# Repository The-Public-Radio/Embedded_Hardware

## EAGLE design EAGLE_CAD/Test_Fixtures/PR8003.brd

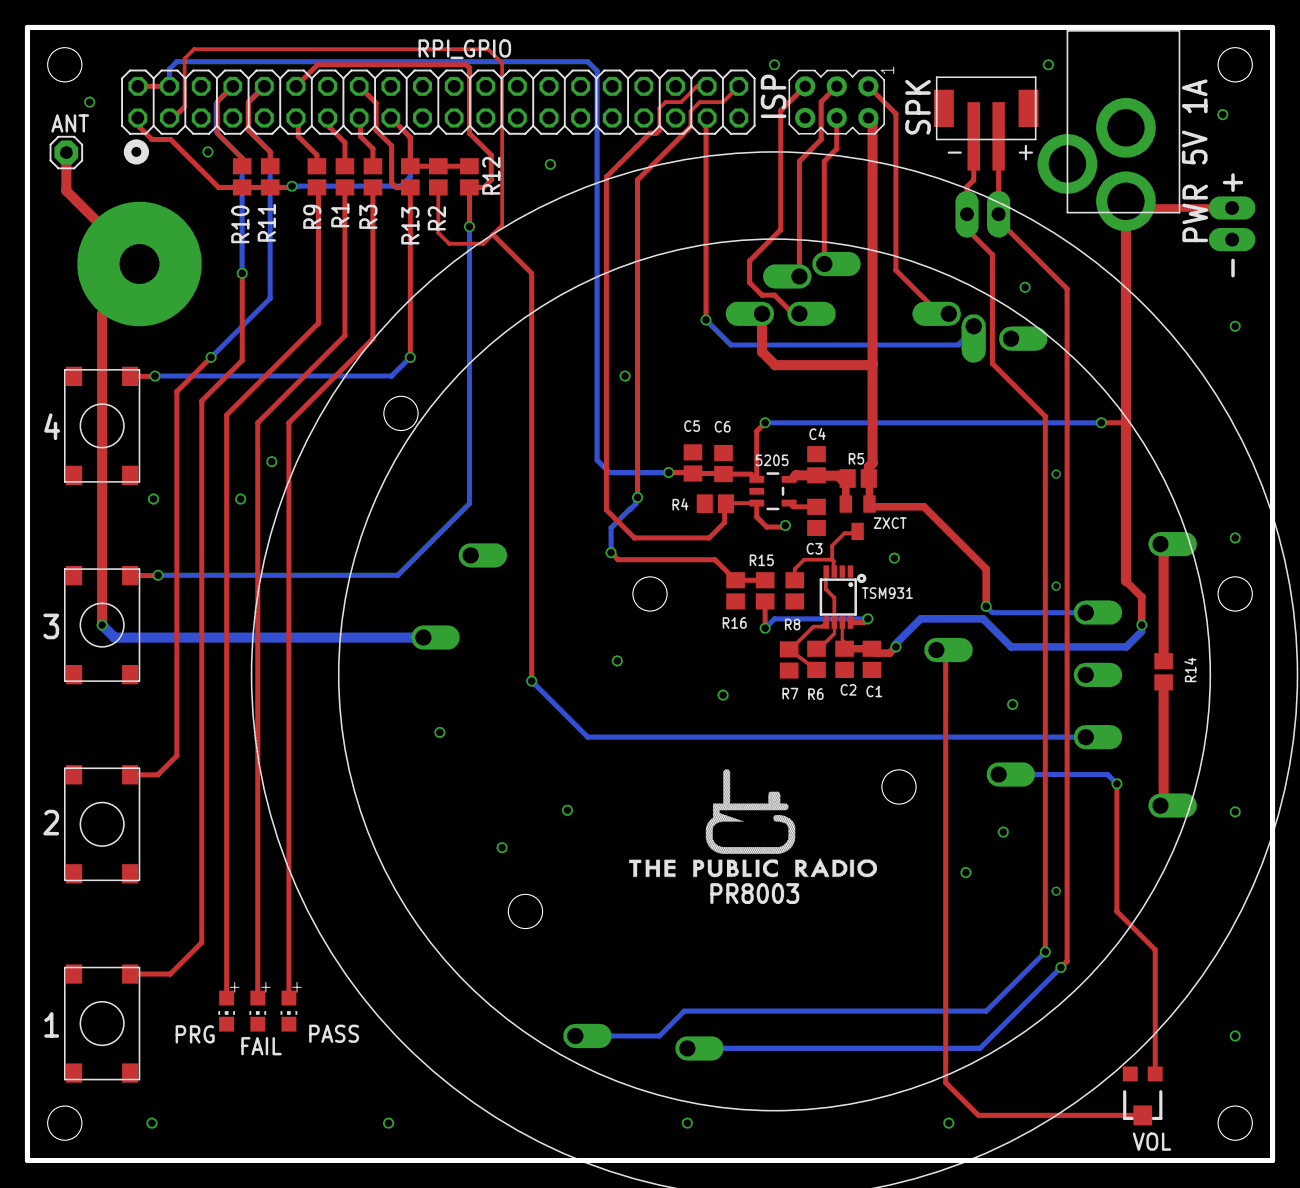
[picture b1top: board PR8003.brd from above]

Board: 2 copper layers, 100.0 x 91.0 mm, 43 parts (0 on the bottom side), 35 nets.

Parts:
5205: MIC5219 3.3V; SOT23-5
ANT: 1X01
C1: 2.2uF; C0805
C2: .1nF; 0805_ADAFRUIT
C3: 470pF; 0805_ADAFRUIT
C4: 4.7uF; C0805
C5: .1uF; 0805_ADAFRUIT
C6: 10nF; C0805
CN1: JST-B2B-PH-SM4-TB
FAIL: CHIP-LED0805
ISP: AVRISP-6; AVRISP
J1: M3_SCREW_POST; M3_BOLT_HOLE
JP2, JP3: M02PTH3; 1X02_LONGPADS
PASS: CHIP-LED0805
PRG: CHIP-LED0805
R1, R3, R9: 1k; 0805_ADAFRUIT
R2, R4, R10, R11, R12, R13: 4.7k; 0805_ADAFRUIT
R5: 2ohm; 0805_ADAFRUIT
R6: 47k; 0805_ADAFRUIT
R7: 2.4M; 0805_ADAFRUIT
R8: 1.5K; 0805_ADAFRUIT
R14: 0 OHM; 0805_ADAFRUIT
R15: 2.2K; 0805_ADAFRUIT
R16: 3.3K; 0805_ADAFRUIT
RPI_GPIO: 2X20
TSM931: TSM931; MSOP8
U$1: PR_LOGO
U$19: 2.1MMJACKTHM; PJ-102A
U$20, U$22, U$23, U$24: C&K_PTS645; C&K_PTS645_SMT
U$26: PR9020_TESTPOINTS
VOL: TC33X
ZXCT: ZXCT1009; SOT23

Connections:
3.3V: ISP.2, R5.1, U$26.P$4, U$26.P$5, ZXCT.1
+3V3: R2.1, R10.1, R11.1, R12.1, R13.1, RPI_GPIO.1, RPI_GPIO.17
+5V: 5205.1, C1.1, C2.1, C5.1, C6.1, JP3.1, RPI_GPIO.2, RPI_GPIO.4, TSM931.7, U$19.TIP
ANT: ANT.1, J1.P$1, U$26.P$18
A_IN: U$26.P$16, VOL.1
A_OUT: U$26.P$17, VOL.2
COMPARATOR: R15.2, R16.1, RPI_GPIO.40
DEV_PRES: R2.2, RPI_GPIO.3, U$26.P$3
FAIL: R1.1, RPI_GPIO.13
GND: 5205.2, C1.2, C2.2, C3.2, C4.2, C5.2, C6.2, FAIL.C, ISP.6, JP3.2, PASS.C, PRG.C, R4.1, R7.2, R8.2, R16.2, RPI_GPIO.6, RPI_GPIO.9, RPI_GPIO.14, RPI_GPIO.20, RPI_GPIO.25, RPI_GPIO.30, RPI_GPIO.34, RPI_GPIO.39, TSM931.1, TSM931.2, U$19.RING, U$20.P$2, U$22.P$2, U$23.P$2, U$24.P$2, U$26.P$1, U$26.P$2, VOL.3
MISO: ISP.1, U$26.P$10
MOSI: ISP.4, U$26.P$13
unnamed: R6.2, TSM931.4, TSM931.6
unnamed: PRG.A, R9.2
unnamed: FAIL.A, R1.2
unnamed: PASS.A, R3.2
unnamed: R15.1, TSM931.8
unnamed: R8.1, TSM931.3, ZXCT.3
unnamed: 5205.4, C3.1
unnamed: 5205.5, C4.1, R5.2, ZXCT.2
unnamed: R6.1, R7.1, TSM931.5
PASS: R3.1, RPI_GPIO.15
PROCESS: R9.1, RPI_GPIO.11
REG_ENABLE: 5205.3, R4.2, RPI_GPIO.38
RST: ISP.5, U$26.P$12
SCK: ISP.3, U$26.P$11
SPK_OUT+: CN1.2, JP2.2, U$26.P$6
SPK_OUT-: CN1.1, JP2.1, U$26.P$7
SW_IN: R14.2, U$26.P$14
SW_OUT: R14.1, U$26.P$15
TAC1: R10.2, RPI_GPIO.8, U$20.P$4
TAC2: R11.2, RPI_GPIO.10, U$23.P$4
TAC3: R12.2, RPI_GPIO.12, U$22.P$4
TAC4: R13.2, RPI_GPIO.16, U$24.P$4
TACSW: RPI_GPIO.37, U$26.P$8

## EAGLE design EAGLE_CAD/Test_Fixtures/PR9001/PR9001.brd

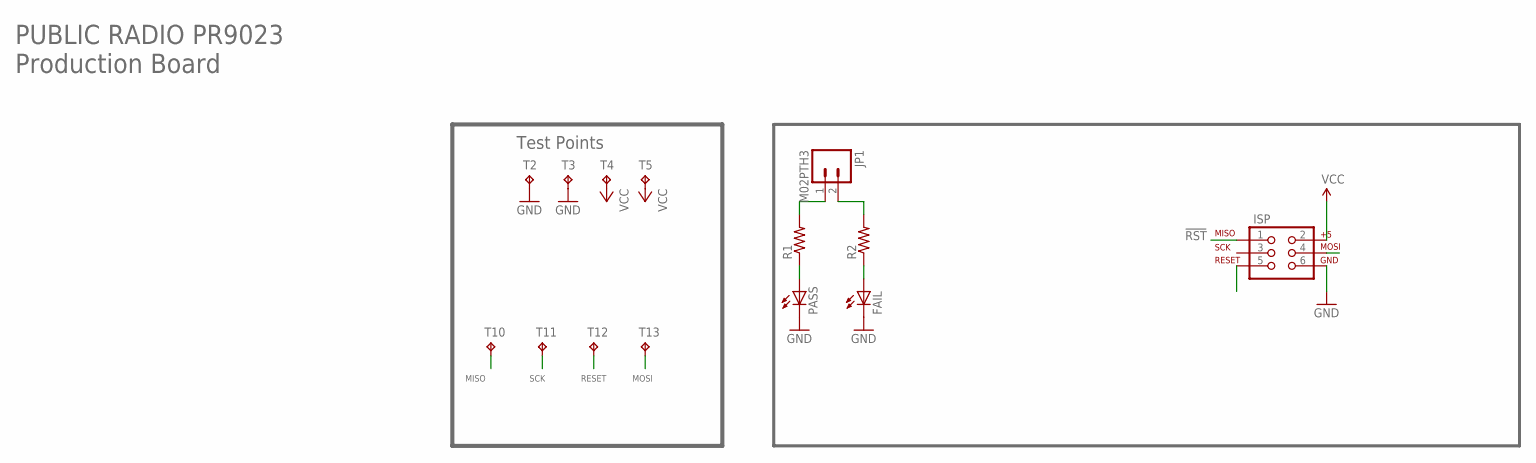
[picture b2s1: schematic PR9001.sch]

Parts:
FAIL: LED5MM
ISP: AVR_SPI_PRG_6NS; 2X3-NS
JP1: M02PTH3; 1X02_LONGPADS
PASS: LED5MM
R1, R2: RESISTORPTH-1/4W-VERT; AXIAL-0.1
T2, T3, T4, T5, T10, T11, T12, T13: PR9001_TESTPOINT

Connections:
!RST: ISP.1, T10.P$1
GND: FAIL.K (C), ISP.6, PASS.K (C), T2.P$1, T3.P$1
unnamed: JP1.2, R2.P$2 (2)
unnamed: PASS.A, R1.P$1 (1)
unnamed: JP1.1, R1.P$2 (2)
unnamed: FAIL.A, R2.P$1 (1)
RESET: ISP.5, T12.P$1
SCLK: ISP.3, T11.P$1
SDIO: ISP.4, T13.P$1
VCC: ISP.2, T4.P$1, T5.P$1

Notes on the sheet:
PUBLIC RADIO PR9023 Production Board
Test Points
MISO
SCK
RESET
MOSI

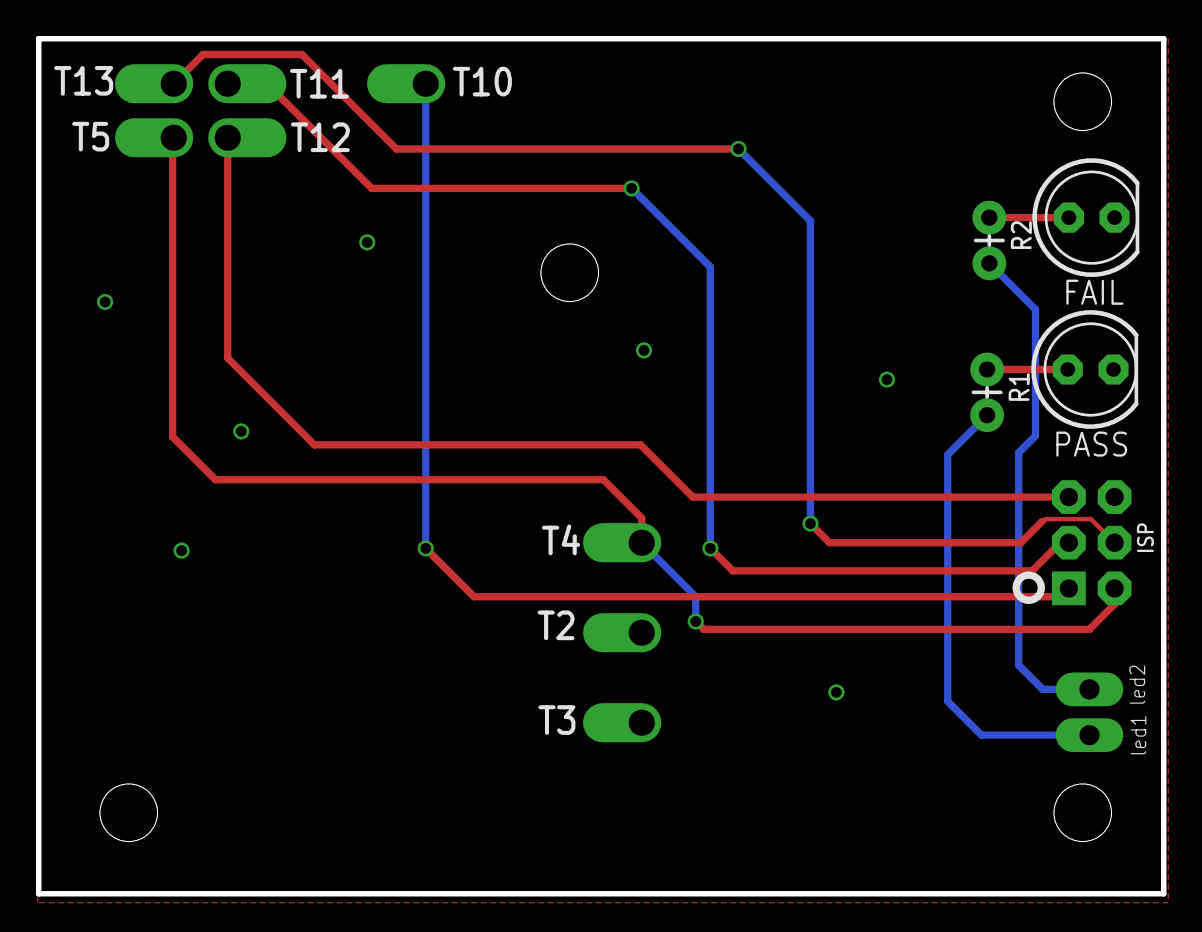
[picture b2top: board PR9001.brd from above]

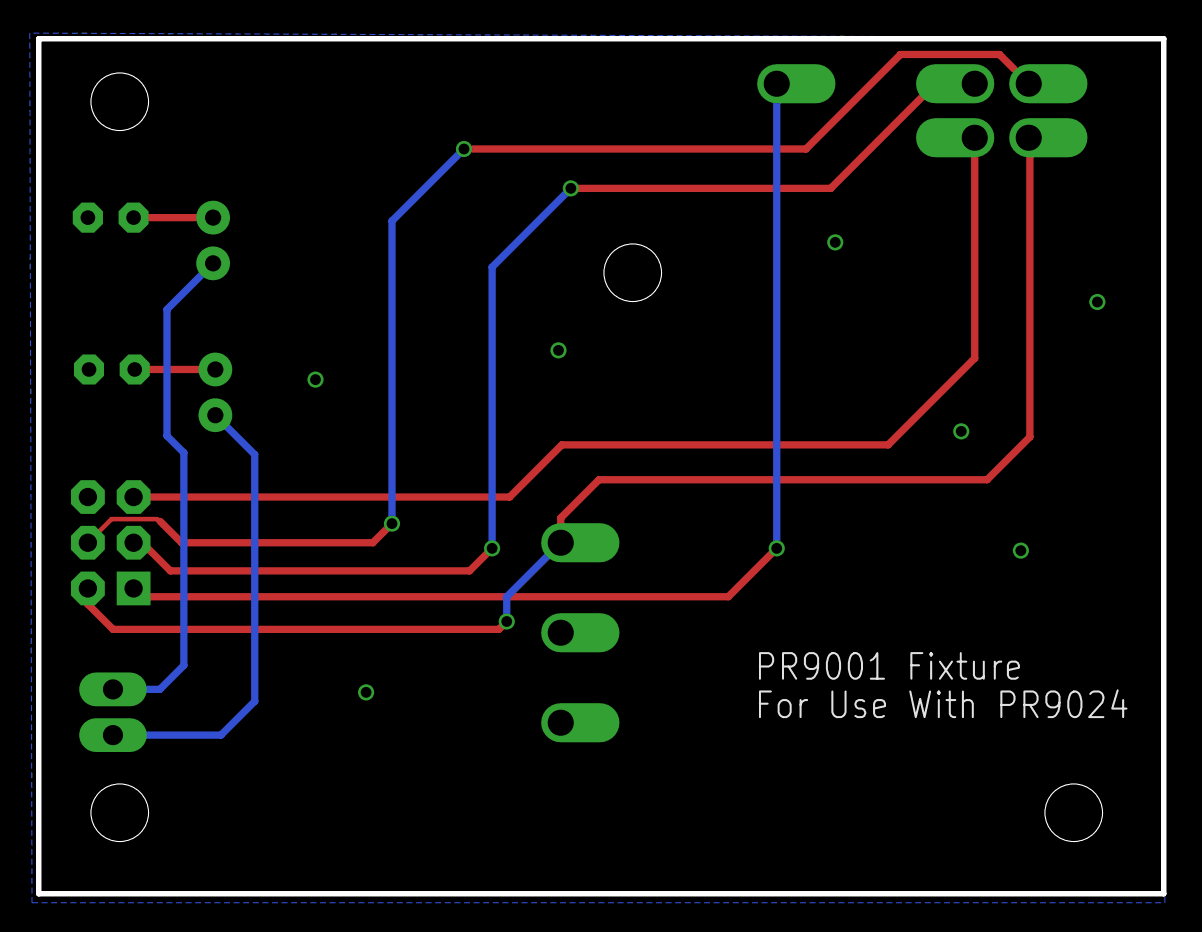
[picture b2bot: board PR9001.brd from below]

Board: 2 copper layers, 62.5 x 47.5 mm, 14 parts (9 on the bottom side), 10 nets.

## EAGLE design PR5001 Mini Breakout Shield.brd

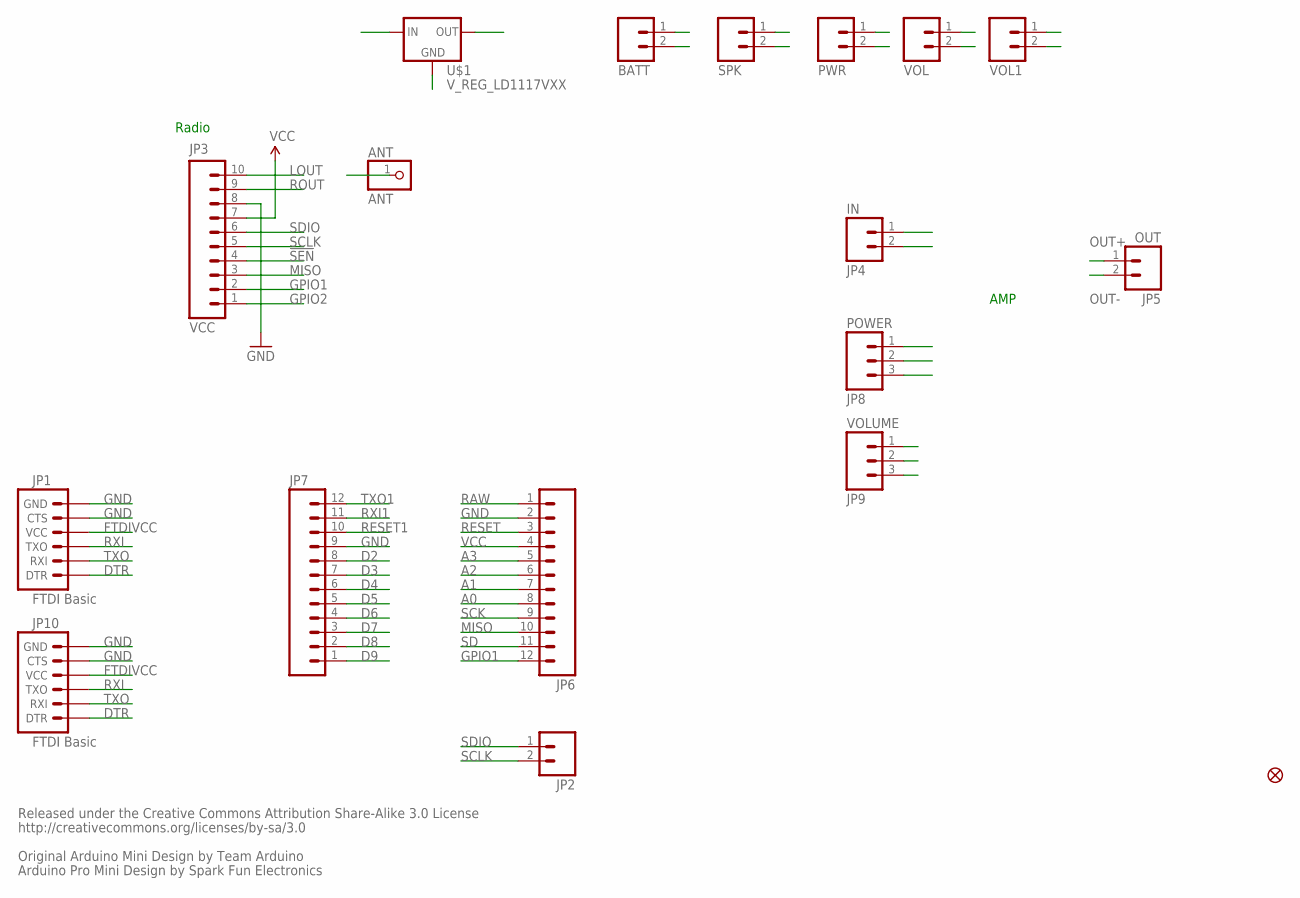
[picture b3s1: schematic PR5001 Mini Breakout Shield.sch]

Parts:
ANT: ANT; 1X01
BATT: M02PTH; 1X02
JP1, JP10: FTDI Basic; 1X06
JP2: M02PTH; 1X02
JP3: VCC; 1X10
JP4: IN; 1X02
JP5: OUT; 1X02
JP6, JP7: M12PTH; 1X12
JP8: POWER; 1X03
JP9: VOLUME; 1X03
PWR: M02PTH; 1X02
SPK: M02PTH; 1X02
U$1: V_REG_LD1117VXX; 78XXL
U$4: FIDUCIAL1X2; FIDUCIAL-1X2
VOL, VOL1: M02PTH; 1X02

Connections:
!SEN: JP3.4
A0: JP6.8
A1: JP6.7
A2: JP6.6
A3: JP6.5
ANT: ANT.1, VOL1.2
BATT+: BATT.1, PWR.1
D2: JP7.8
D3: JP7.7
D4: JP7.6
D5: JP7.5
D6: JP7.4
D7: JP7.3
D8: JP7.2
D9: JP7.1
DTR: JP1.1 (DTR), JP10.1 (DTR)
FTDIVCC: JP1.4 (VCC), JP10.4 (VCC)
GND: BATT.2, JP1.5 (CTS), JP1.6 (GND), JP3.8, JP4.2, JP6.2, JP7.9, JP8.1, JP9.1, JP10.5 (CTS), JP10.6 (GND), U$1.IN (GND), VOL.1
GPIO1: JP3.2, JP6.12
GPIO2: JP3.1
IN: JP9.3, VOL1.1
LOUT: JP3.10, JP4.1
MISO: JP3.3, JP6.10
OPUT: JP9.2, VOL.2
OUT+: JP5.1, SPK.1
OUT-: JP5.2, SPK.2
POT+: PWR.2, U$1.OUT (IN)
RAW: JP6.1
RESET: JP6.3
RESET1: JP7.10
ROUT: JP3.9
RXI: JP1.3 (TXO), JP10.3 (TXO)
RXI1: JP7.11
SCK: JP6.9
SCLK: JP2.2, JP3.5
SD: JP6.11, JP8.3
SDIO: JP2.1, JP3.6
TXO: JP1.2 (RXI), JP10.2 (RXI)
TXO1: JP7.12
VCC: JP3.7, JP6.4, JP8.2, U$1.GND (OUT)

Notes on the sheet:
Released under the Creative Commons Attribution Share-Alike 3.0 License
http://creativecommons.org/licenses/by-sa/3.0
Original Arduino Mini Design by Team Arduino
Arduino Pro Mini Design by Spark Fun Electronics
AMP
Radio

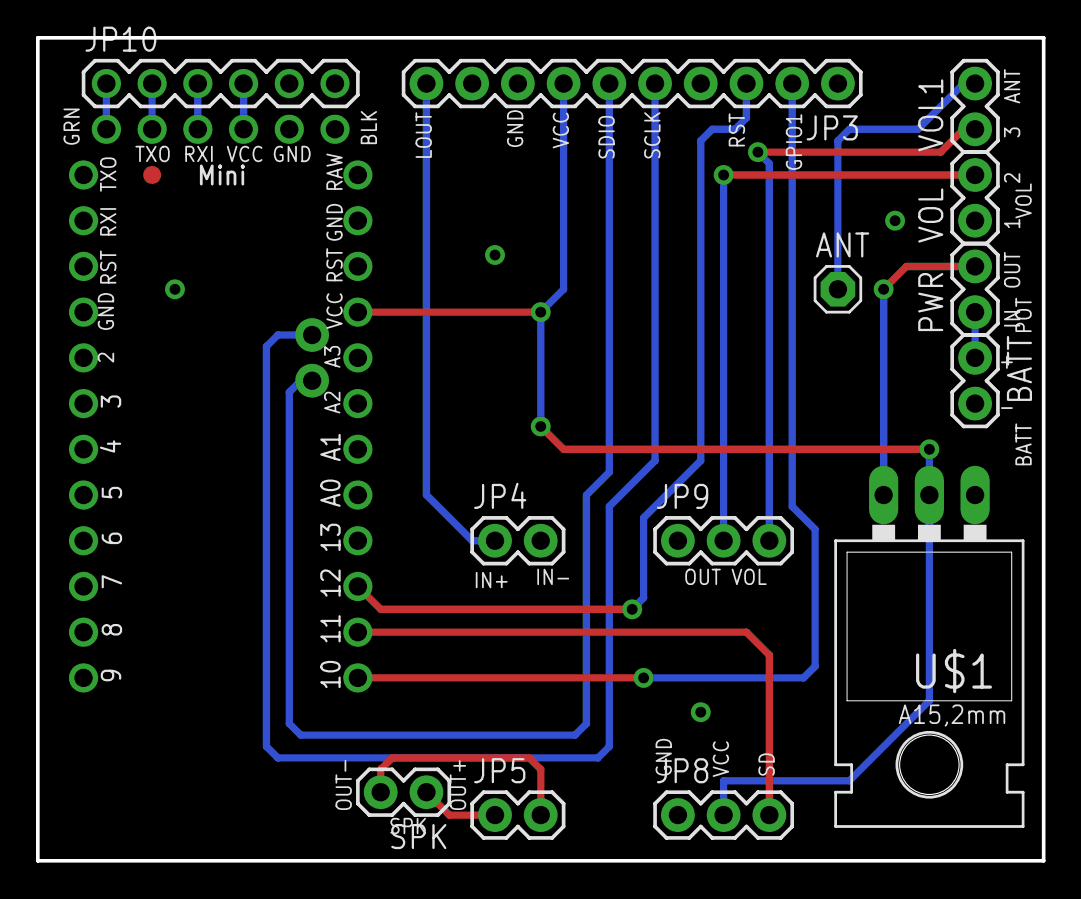
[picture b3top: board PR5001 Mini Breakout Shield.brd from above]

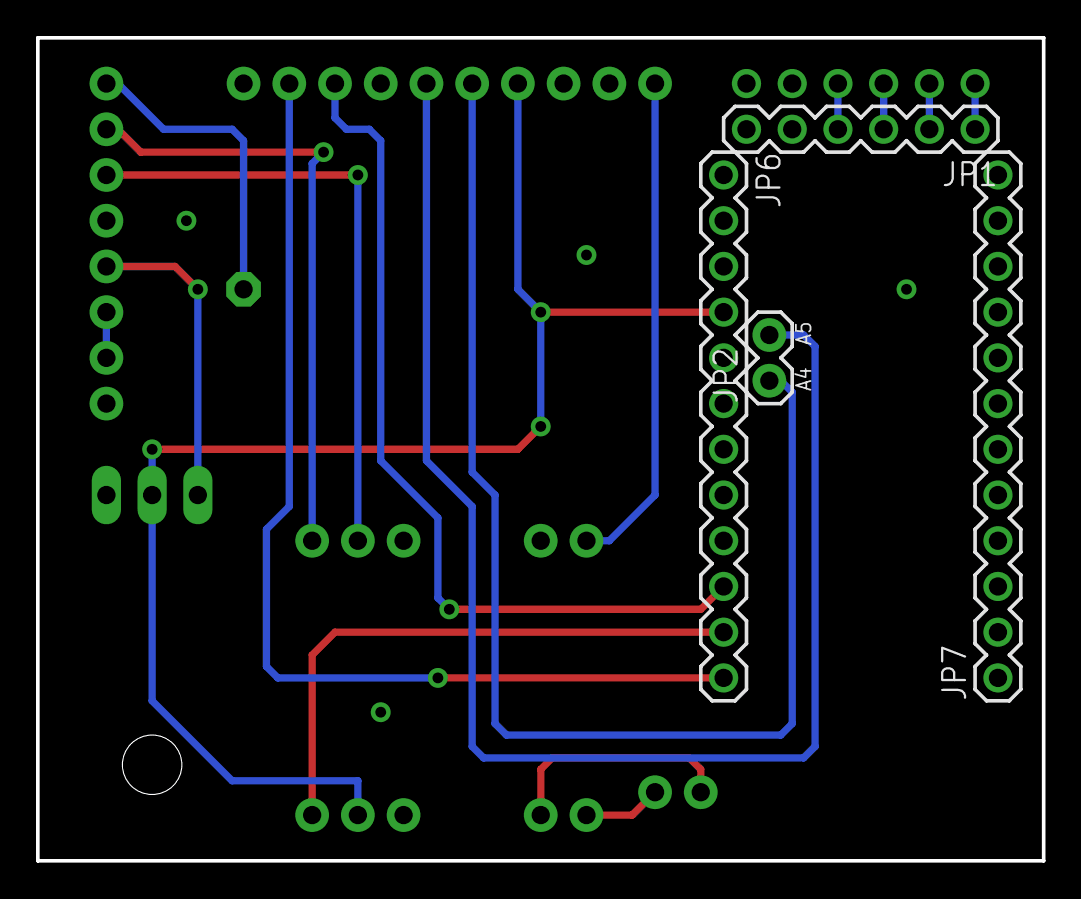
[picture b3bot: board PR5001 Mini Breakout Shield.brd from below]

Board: 2 copper layers, 55.9 x 45.7 mm, 18 parts (4 on the bottom side), 19 nets.

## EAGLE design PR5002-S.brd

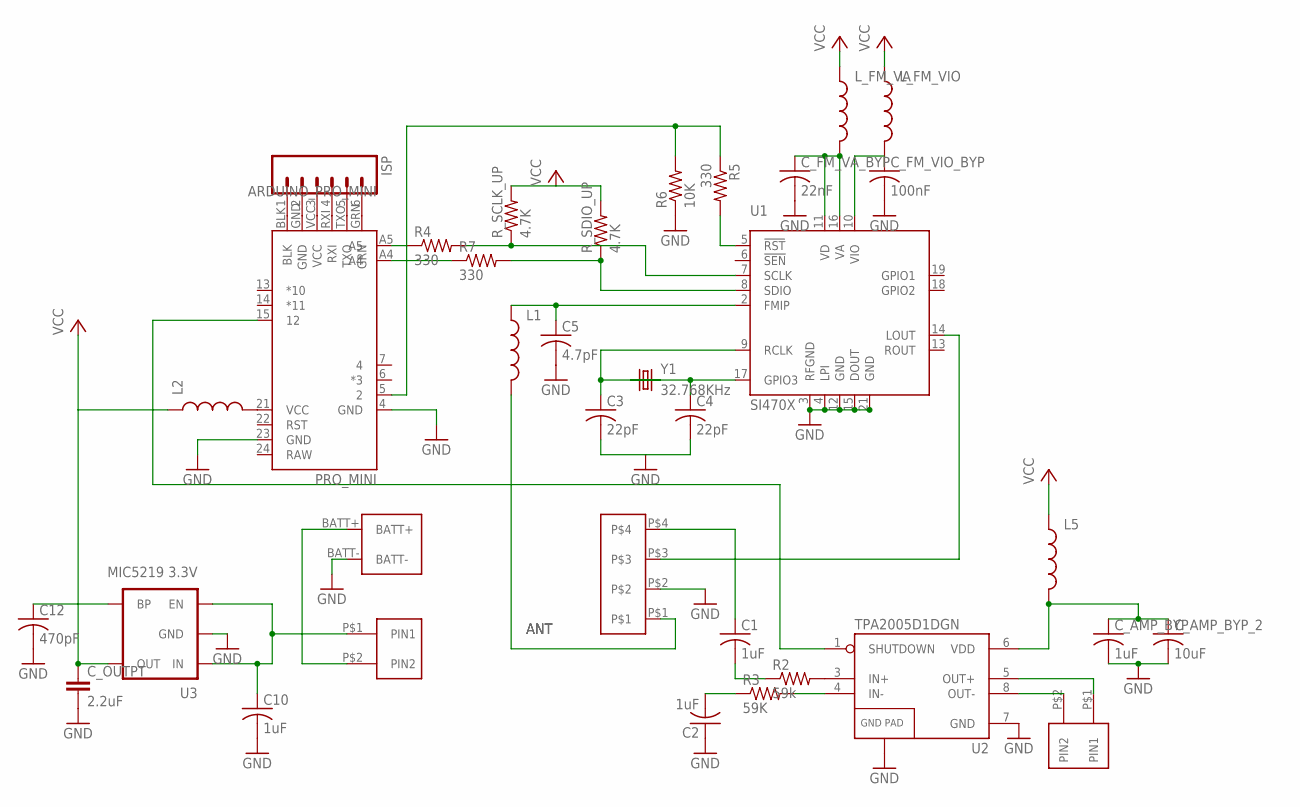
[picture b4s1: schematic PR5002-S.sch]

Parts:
ANT/POT_VOL: OSTVN04
BATT_IN: KEYSTONE_2479_3XAAA_BOTTOM
C1, C2, C10: 1uF; C0603
C3, C4: 22pF; C0603
C5: 4.7pF; C0603
C12: 470pF; C0603
C_AMP_BYP: 1uF; C0603
C_AMP_BYP_2: 10uF; C0603
C_FM_VA_BYP: 22nF; C0603
C_FM_VIO_BYP: 100nF; C0603
C_OUTPT: 2.2uF; VISHAY_TR3C
ISP: M06LOCK_LONGPADS; 1X06_LOCK_LONGPADS
L1: INDUCTOR0805; 0805
L2, L5: INDUCTOR0603; 0603
L_FM_VA: INDUCTOR0603; 0603
L_FM_VIO: INDUCTOR0603; 0603
POT_SW: OSTVN02
PRO_MINI: ARDUINO_PRO_MINI
R2: 59k; R0603
R3: 59K; R0603
R4, R5, R7: 330; R0603
R6: 10K; R0603
R_SCLK_UP: 4.7K; R0603
R_SDIO_UP: 4.7K; R0603
SPKR: OSTVN02
U1: SI470X
U2: TPA2005D1DGN; POWER-SOP8
U3: MIC5219 3.3V; SOT23-5
Y1: 32.768KHz; CRYSTAL-32KHZ-SMD

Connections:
ANT: ANT/POT_VOL.P$1, L1.2
BATT+: BATT_IN.BATT+, POT_SW.P$2 (PIN2)
GND: ANT/POT_VOL.P$2, BATT_IN.BATT-, C2.1, C3.2, C4.2, C5.2, C10.2, C12.2, C_AMP_BYP.2, C_AMP_BYP_2.2, C_FM_VA_BYP.2, C_FM_VIO_BYP.2, C_OUTPT.P$2 (2), PRO_MINI.4 (GND), PRO_MINI.23 (GND), R6.1, U1.3 (RFGND), U1.4 (LPI), U1.12 (GND), U1.15 (DOUT), U1.21 (GND), U2.7 (GND), U2.9 (GND), U3.2 (GND)
unnamed: C2.2, R3.1
unnamed: C1.2, R2.1
unnamed: C3.1, U1.9 (RCLK), Y1.X2 (2)
unnamed: R5.2, U1.5 (!RST)
unnamed: PRO_MINI.A5, R4.1
unnamed: R4.2, R_SCLK_UP.1, U1.7 (SCLK)
unnamed: PRO_MINI.A4, R7.1
unnamed: PRO_MINI.5 (2), R5.1, R6.2
unnamed: R7.2, R_SDIO_UP.1, U1.8 (SDIO)
unnamed: C5.1, L1.1, U1.2 (FMIP)
unnamed: C4.1, U1.17 (GPIO3), Y1.X1 (1)
unnamed: ISP.6, PRO_MINI.GRN
unnamed: ISP.5, PRO_MINI.TXO
unnamed: R2.2, U2.3 (IN+)
unnamed: R3.2, U2.4 (IN-)
unnamed: SPKR.P$2 (PIN2), U2.8 (OUT-)
unnamed: SPKR.P$1 (PIN1), U2.5 (OUT+)
unnamed: ISP.4, PRO_MINI.RXI
unnamed: ANT/POT_VOL.P$3, U1.14 (LOUT)
unnamed: C10.1, POT_SW.P$1 (PIN1), U3.1 (IN), U3.3 (EN)
unnamed: ISP.3, PRO_MINI.VCC
unnamed: ISP.2, PRO_MINI.GND
unnamed: ISP.1, PRO_MINI.BLK
unnamed: PRO_MINI.15 (12), U2.1 (SHUTDOWN)
unnamed: ANT/POT_VOL.P$4, C1.1
unnamed: C12.1, U3.4 (BP)
unnamed: L2.2, PRO_MINI.21 (VCC)
unnamed: C_FM_VIO_BYP.1, L_FM_VIO.2, U1.10 (VIO)
unnamed: C_FM_VA_BYP.1, L_FM_VA.2, U1.11 (VD), U1.16 (VA)
unnamed: C_AMP_BYP.1, C_AMP_BYP_2.1, L5.2, U2.6 (VDD)
VCC: C_OUTPT.P$1 (1), L2.1, L5.1, L_FM_VA.1, L_FM_VIO.1, R_SCLK_UP.2, R_SDIO_UP.2, U3.5 (OUT)

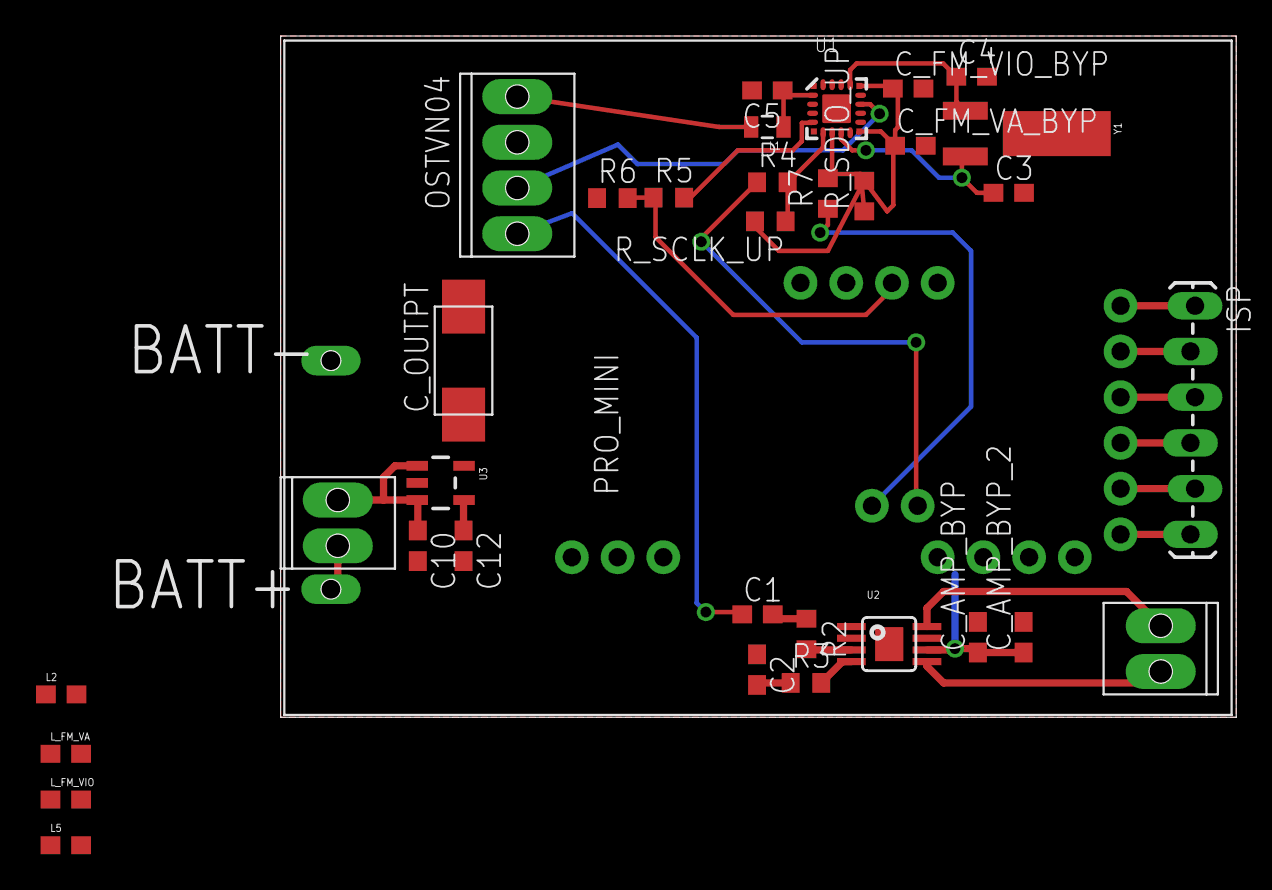
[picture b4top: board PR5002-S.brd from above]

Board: 2 copper layers, 53.1 x 37.8 mm, 35 parts (0 on the bottom side), 34 nets.

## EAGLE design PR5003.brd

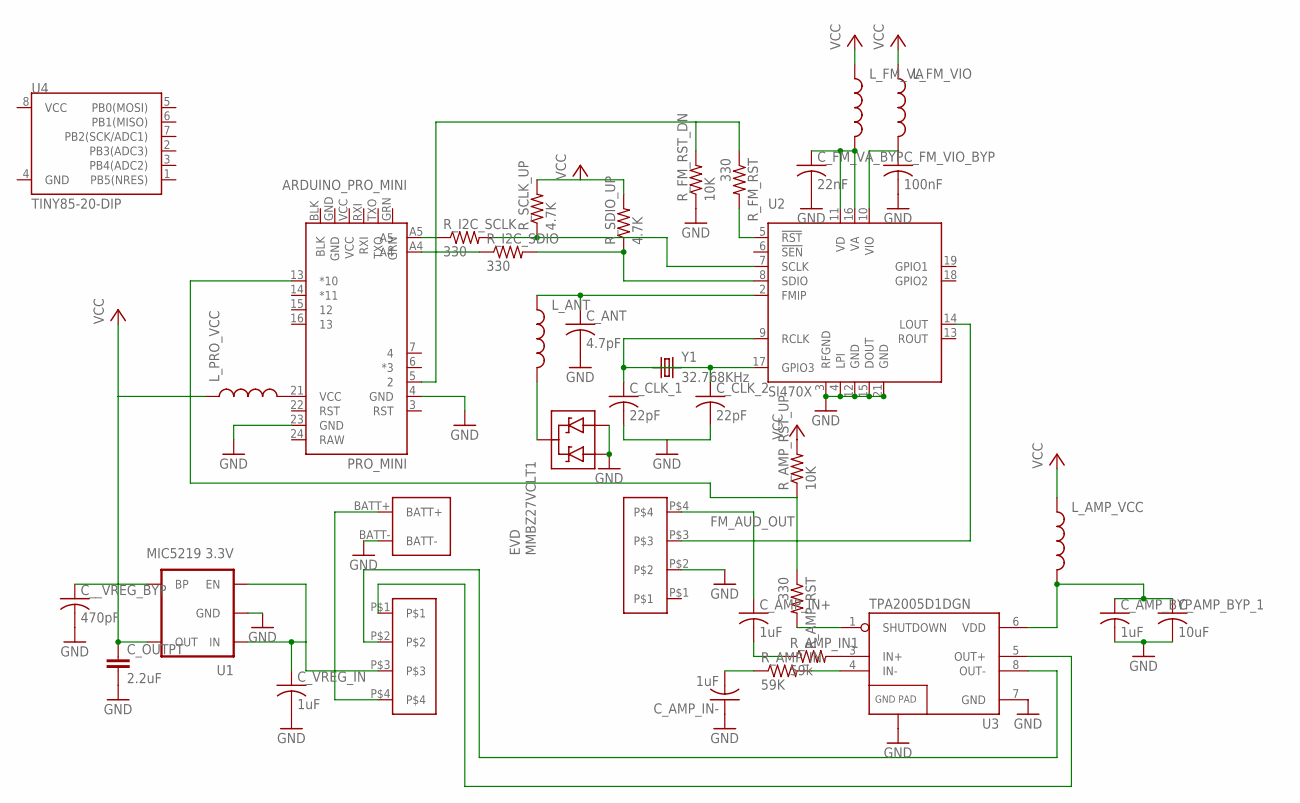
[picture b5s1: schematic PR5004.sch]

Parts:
ANT/POT_VOL, ANT/POT_VOL1: OSTVN04
BATT_IN: KEYSTONE_2479_3XAAA_BOTTOM
C_AMP_BYP: 1uF; C0603
C_AMP_BYP_1: 10uF; C0603
C_AMP_IN+: 1uF; C0603
C_AMP_IN-: 1uF; C0603
C_ANT: 4.7pF; C0805
C_CLK_1, C_CLK_2: 22pF; C0603
C_FM_VA_BYP: 22nF; C0603
C_FM_VIO_BYP: 100nF; C0603
C_OUTPT: 2.2uF; VISHAY_TR3C
C_VREG_IN: 1uF; C0603
C__VREG_BYP: 470pF; C0603
EVD: MMBZ27VCLT1; SOT23-3
L_AMP_VCC: INDUCTOR0603; 0603
L_ANT: INDUCTOR0805; 0805
L_FM_VA: INDUCTOR0603; 0603
L_FM_VIO: INDUCTOR0603; 0603
L_PRO_VCC: INDUCTOR0603; 0603
PRO_MINI: ARDUINO_PRO_MINI
R_AMP_IN1: 59k; R0603
R_AMP_IN-: 59K; R0603
R_AMP_RST: 330; R0603
R_AMP_RST_UP: 10K; R0603
R_FM_RST: 330; R0603
R_FM_RST_DN: 10K; R0603
R_I2C_SCLK, R_I2C_SDIO: 330; R0603
R_SCLK_UP: 4.7K; R0603
R_SDIO_UP: 4.7K; R0603
U1: MIC5219 3.3V; SOT23-5
U2: SI470X
U3: TPA2005D1DGN; POWER-SOP8
U4: TINY85-20-DIP; DIP08
Y1: 32.768KHz; CRYSTAL-32KHZ-SMD

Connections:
ANT: ANT/POT_VOL.P$1, EVD.3 (C), L_ANT.2
BATT+: ANT/POT_VOL1.P$4, BATT_IN.BATT+
FM_AUD_OUT: ANT/POT_VOL.P$3, U2.14 (LOUT)
GND: ANT/POT_VOL.P$2, BATT_IN.BATT-, C_AMP_BYP.2, C_AMP_BYP_1.2, C_AMP_IN-.1, C_ANT.2, C_CLK_1.2, C_CLK_2.2, C_FM_VA_BYP.2, C_FM_VIO_BYP.2, C_OUTPT.P$2 (2), C_VREG_IN.2, C__VREG_BYP.2, EVD.1 (A1), EVD.2 (A2), PRO_MINI.4 (GND), PRO_MINI.23 (GND), PRO_MINI.BLK, PRO_MINI.GND, R_FM_RST_DN.1, U1.2 (GND), U2.3 (RFGND), U2.4 (LPI), U2.12 (GND), U2.15 (DOUT), U2.21 (GND), U3.7 (GND), U3.9 (GND); also elsewhere on the board
unnamed: C_AMP_IN-.2, R_AMP_IN-.1
unnamed: C_AMP_IN+.2, R_AMP_IN1.1
unnamed: C_CLK_1.1, U2.9 (RCLK), Y1.X2 (2)
unnamed: R_FM_RST.2, U2.5 (!RST)
unnamed: PRO_MINI.A5, R_I2C_SCLK.1
unnamed: R_I2C_SCLK.2, R_SCLK_UP.1, U2.7 (SCLK)
unnamed: PRO_MINI.A4, R_I2C_SDIO.1
unnamed 11: PRO_MINI.15 (12); also elsewhere on the board
unnamed: R_I2C_SDIO.2, R_SDIO_UP.1, U2.8 (SDIO)
unnamed: C_ANT.1, L_ANT.1, U2.2 (FMIP)
unnamed: C_CLK_2.1, U2.17 (GPIO3), Y1.X1 (1)
unnamed 15: PRO_MINI.GRN; also elsewhere on the board
unnamed 16: PRO_MINI.TXO; also elsewhere on the board
unnamed: R_AMP_IN1.2, U3.3 (IN+)
unnamed: R_AMP_IN-.2, U3.4 (IN-)
unnamed: ANT/POT_VOL1.P$2, U3.8 (OUT-)
unnamed: ANT/POT_VOL1.P$1, U3.5 (OUT+)
unnamed 21: PRO_MINI.RXI; also elsewhere on the board
unnamed: R_AMP_RST.2, U3.1 (SHUTDOWN)
unnamed: ANT/POT_VOL1.P$3, C_VREG_IN.1, U1.1 (IN), U1.3 (EN)
unnamed 24: PRO_MINI.VCC; also elsewhere on the board
unnamed 25: PRO_MINI.3 (RST); also elsewhere on the board
unnamed: PRO_MINI.5 (2), R_FM_RST.1, R_FM_RST_DN.2
unnamed 27: PRO_MINI.14 (*11); also elsewhere on the board
unnamed: PRO_MINI.13 (*10), R_AMP_RST.1, R_AMP_RST_UP.1
unnamed 29: PRO_MINI.16 (13); also elsewhere on the board
unnamed: ANT/POT_VOL.P$4, C_AMP_IN+.1
unnamed: C__VREG_BYP.1, U1.4 (BP)
unnamed: L_PRO_VCC.2, PRO_MINI.21 (VCC)
unnamed: C_FM_VIO_BYP.1, L_FM_VIO.2, U2.10 (VIO)
unnamed: C_FM_VA_BYP.1, L_FM_VA.2, U2.11 (VD), U2.16 (VA)
unnamed: C_AMP_BYP.1, C_AMP_BYP_1.1, L_AMP_VCC.2, U3.6 (VDD)
VCC: C_OUTPT.P$1 (1), L_AMP_VCC.1, L_FM_VA.1, L_FM_VIO.1, L_PRO_VCC.1, R_AMP_RST_UP.2, R_SCLK_UP.2, R_SDIO_UP.2, U1.5 (OUT); also elsewhere on the board

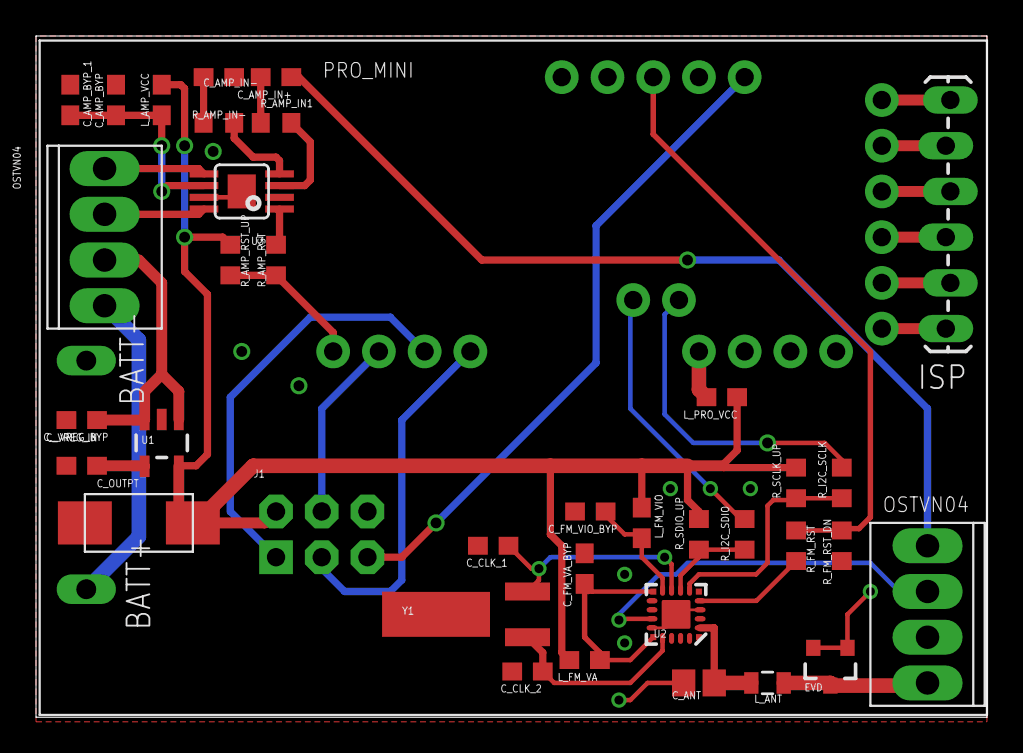
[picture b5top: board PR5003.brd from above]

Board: 2 copper layers, 52.8 x 37.8 mm, 38 parts (0 on the bottom side), 37 nets.

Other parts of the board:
ISP: 1X06_LOCK_LONGPADS
J1: AVR_SPI_PRG_6NS; 2X3-NS

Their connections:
GND: ISP.1, ISP.2, J1.6; also elsewhere on the board
unnamed 11: J1.1; also elsewhere on the board
unnamed 15: ISP.6; also elsewhere on the board
unnamed 16: ISP.5; also elsewhere on the board
unnamed 21: ISP.4; also elsewhere on the board
unnamed 24: ISP.3; also elsewhere on the board
unnamed 25: J1.5; also elsewhere on the board
unnamed 27: J1.4; also elsewhere on the board
unnamed 29: J1.3; also elsewhere on the board
VCC: J1.2; also elsewhere on the board

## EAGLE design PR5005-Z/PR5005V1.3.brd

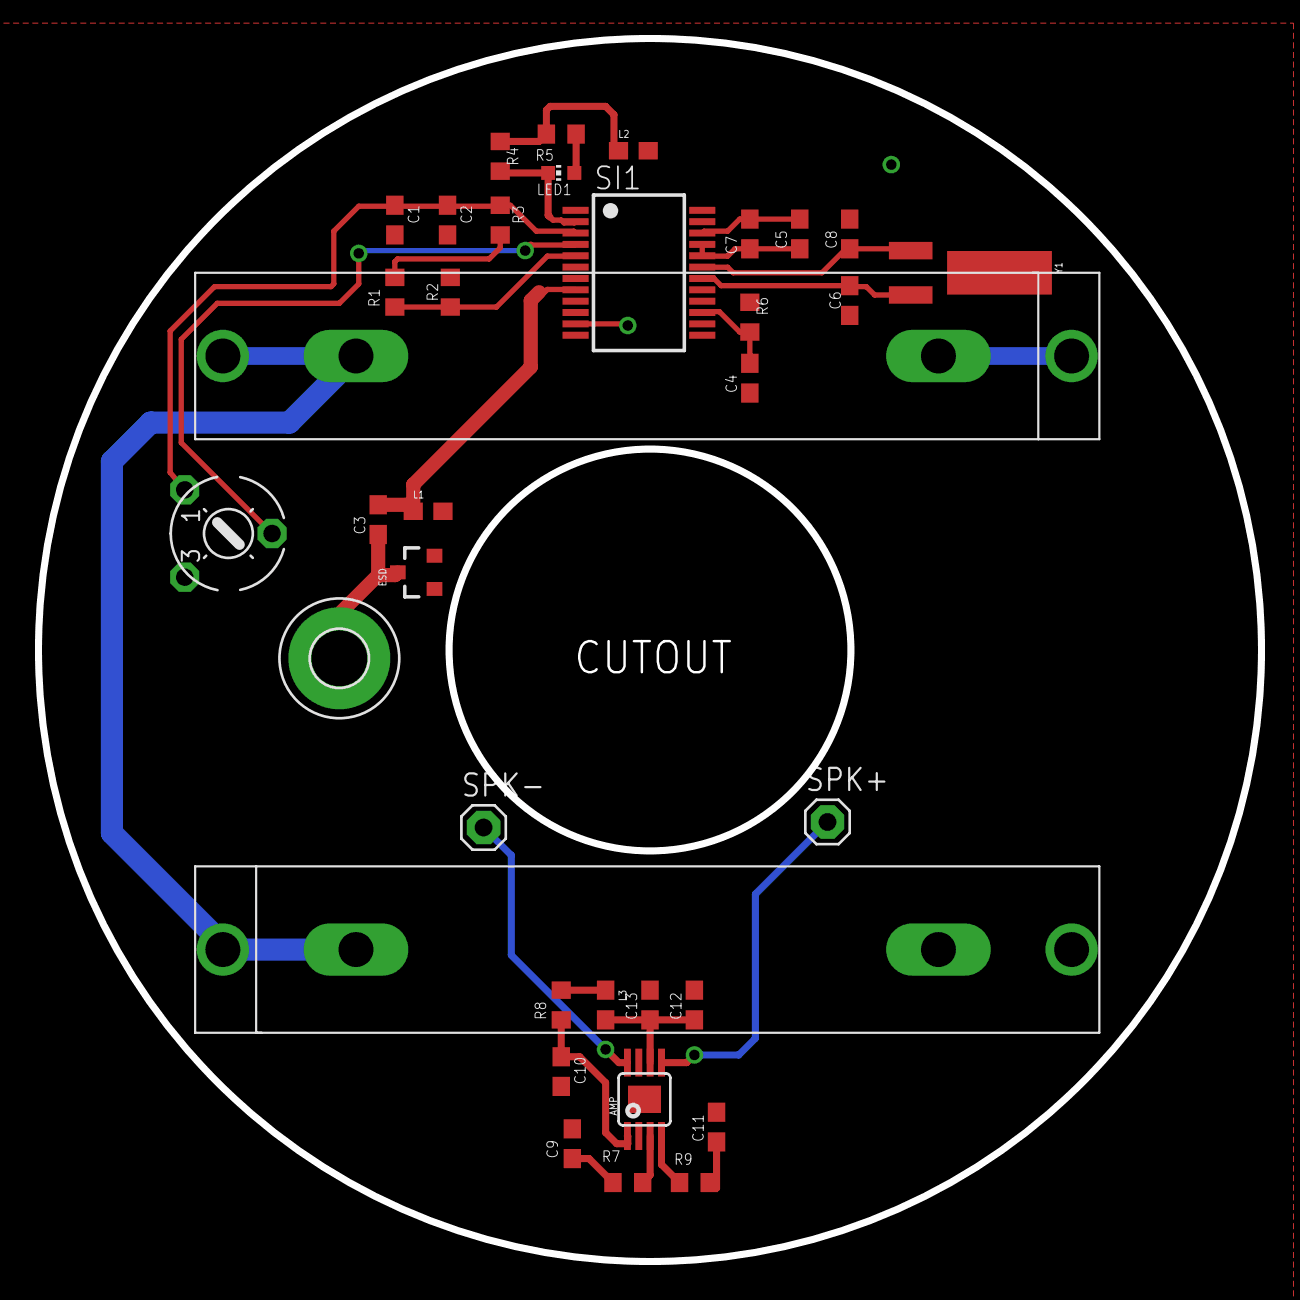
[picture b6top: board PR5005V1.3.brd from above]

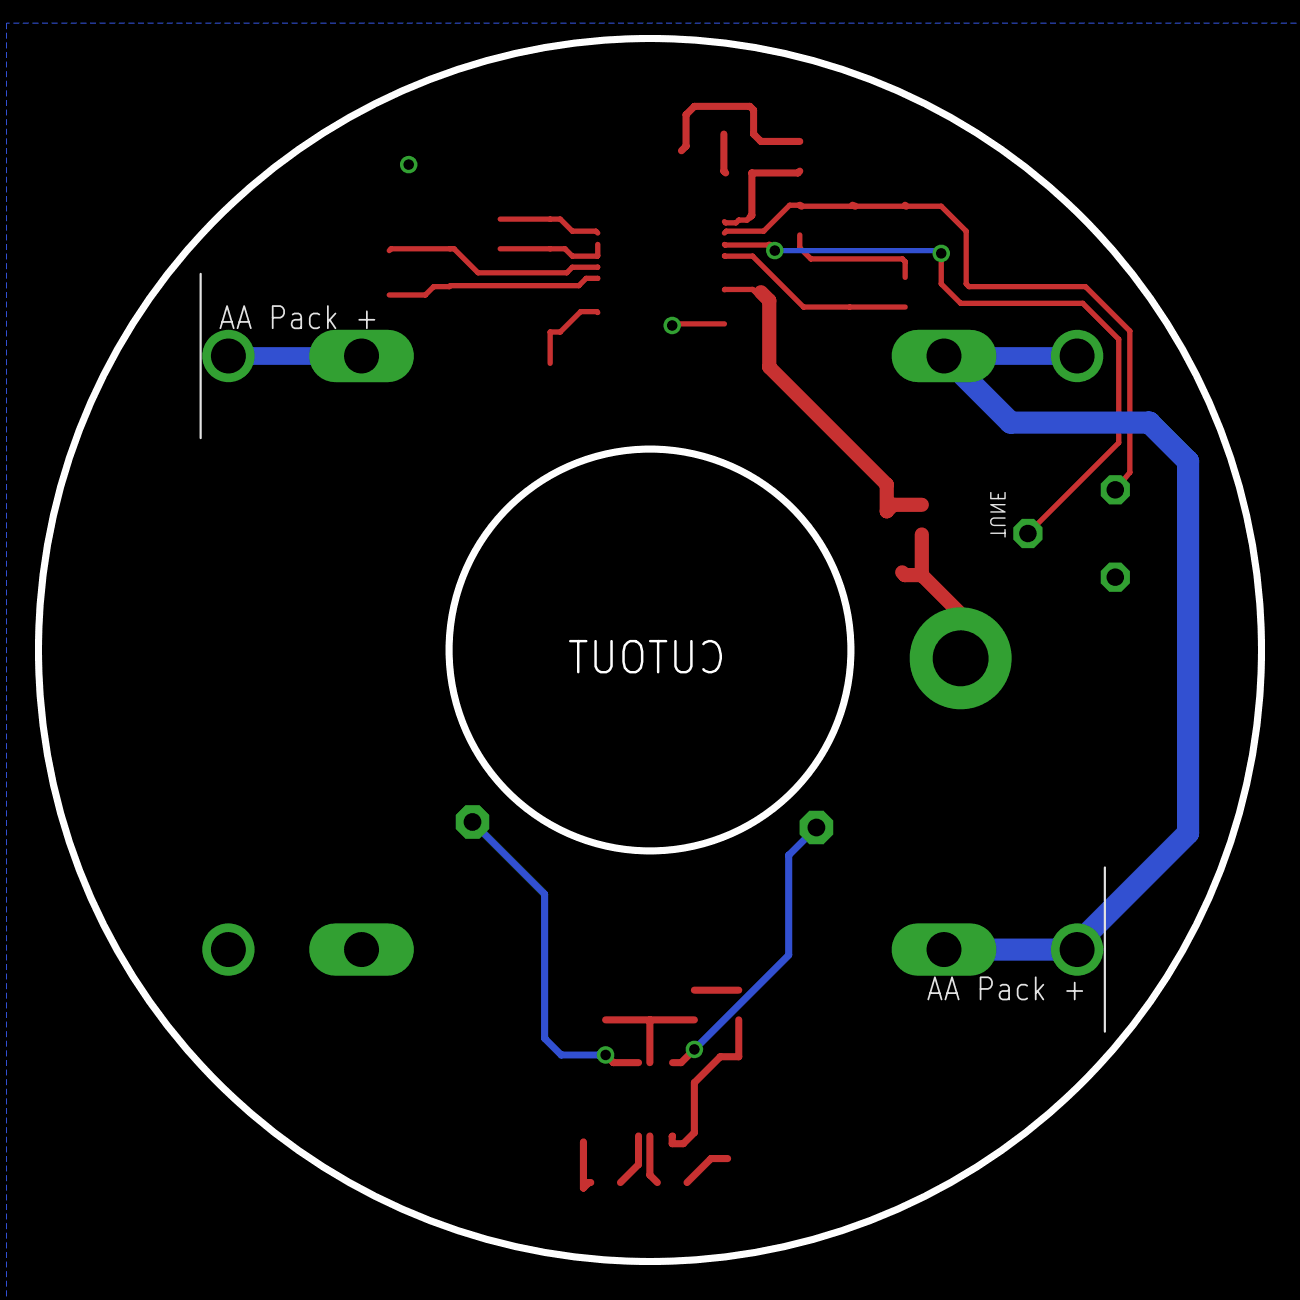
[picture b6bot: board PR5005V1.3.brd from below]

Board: 2 copper layers, 70.0 x 70.0 mm, 36 parts (2 on the bottom side), 25 nets.

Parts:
AMP: TPA2005D1DGN; POWER-SOP8
C1: 47uF; C0603
C2: .1uF; C0603
C3: 1nF; C0603
C4, C5: .1uf; C0603
C6, C8: 22pF; C0603
C7: 4.7uf; C0603
C9, C11, C13: 1uf; C0603
C10, C12: 10uf; C0603
ESD: MMBZ27VCLT1; SOT23-3
FM_ANT: MOUNT-PAD-ROUND3.2; 3,2-PAD
L1: 56nH; 0603
L2, L3: 0603
LED1: CHIP-LED0603
R1: 412K; R0603
R2: 77K; R0603
R3: 1K; R0603
R4, R8: 10K; R0603
R5: 220; R0603
R6: 100K; R0603
R7, R9: 59K; R0603
SI1: SI4831-SSOP-24
SPK+: 1X01
SPK-: 1X01
TUNE: 100K; 6MM
U$1, U$2: MPD-BK-92-AA-CLIP
Y1: CRYSTAL-32KHZ-SMD

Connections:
GND: AMP.7, AMP.9, C1.2, C2.2, C4.1, C6.2, C8.2, C10.2, C11.2, C12.2, C13.2, ESD.1, ESD.2, L1.2, R2.1, SI1.9, SI1.10, SI1.11, SI1.13, SI1.14, SI1.16, SI1.17, TUNE.E, U$2.-, U$2.-1
unnamed: AMP.3, R7.2
unnamed: AMP.4, R9.2
unnamed: C11.1, R9.1
unnamed: C9.2, R7.1
unnamed: C9.1, SI1.24
unnamed: C5.2, C7.2, SI1.22
unnamed: C8.1, SI1.19, Y1.X1
unnamed: C4.2, R6.1, SI1.15
unnamed: LED1.C, R4.1, SI1.2
unnamed: C6.1, SI1.18, Y1.X2
unnamed: LED1.A, R5.1
unnamed: SI1.4, TUNE.S
unnamed: R1.1, R2.2, SI1.5
unnamed: U$1.-, U$1.-1, U$2.+, U$2.+1
unnamed: C3.2, L1.1, SI1.8
unnamed: C5.1, C7.1, L2.2, SI1.20, SI1.21
unnamed: AMP.6, C12.1, C13.1, L3.2
unnamed: AMP.1, C10.1, R8.1
unnamed: C3.1, ESD.3, FM_ANT.B3,2
unnamed: R1.2, R3.1
unnamed: C1.1, C2.1, R3.2, SI1.3, TUNE.A
unnamed: AMP.5, SPK+.1
unnamed: AMP.8, SPK-.1
VCC: L2.1, L3.1, R4.2, R5.2, R6.2, R8.2, U$1.+, U$1.+1

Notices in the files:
parts and their libraries:
SparkFun-Aesthetics: Licensing: CC v3.0 Share-Alike You are welcome to use this library for commercial purposes.
SparkFun-PowerIC: Licensing: Creative Commons ShareAlike 4.0 International - https://creativecommons.org/licenses/by-sa/4.0
